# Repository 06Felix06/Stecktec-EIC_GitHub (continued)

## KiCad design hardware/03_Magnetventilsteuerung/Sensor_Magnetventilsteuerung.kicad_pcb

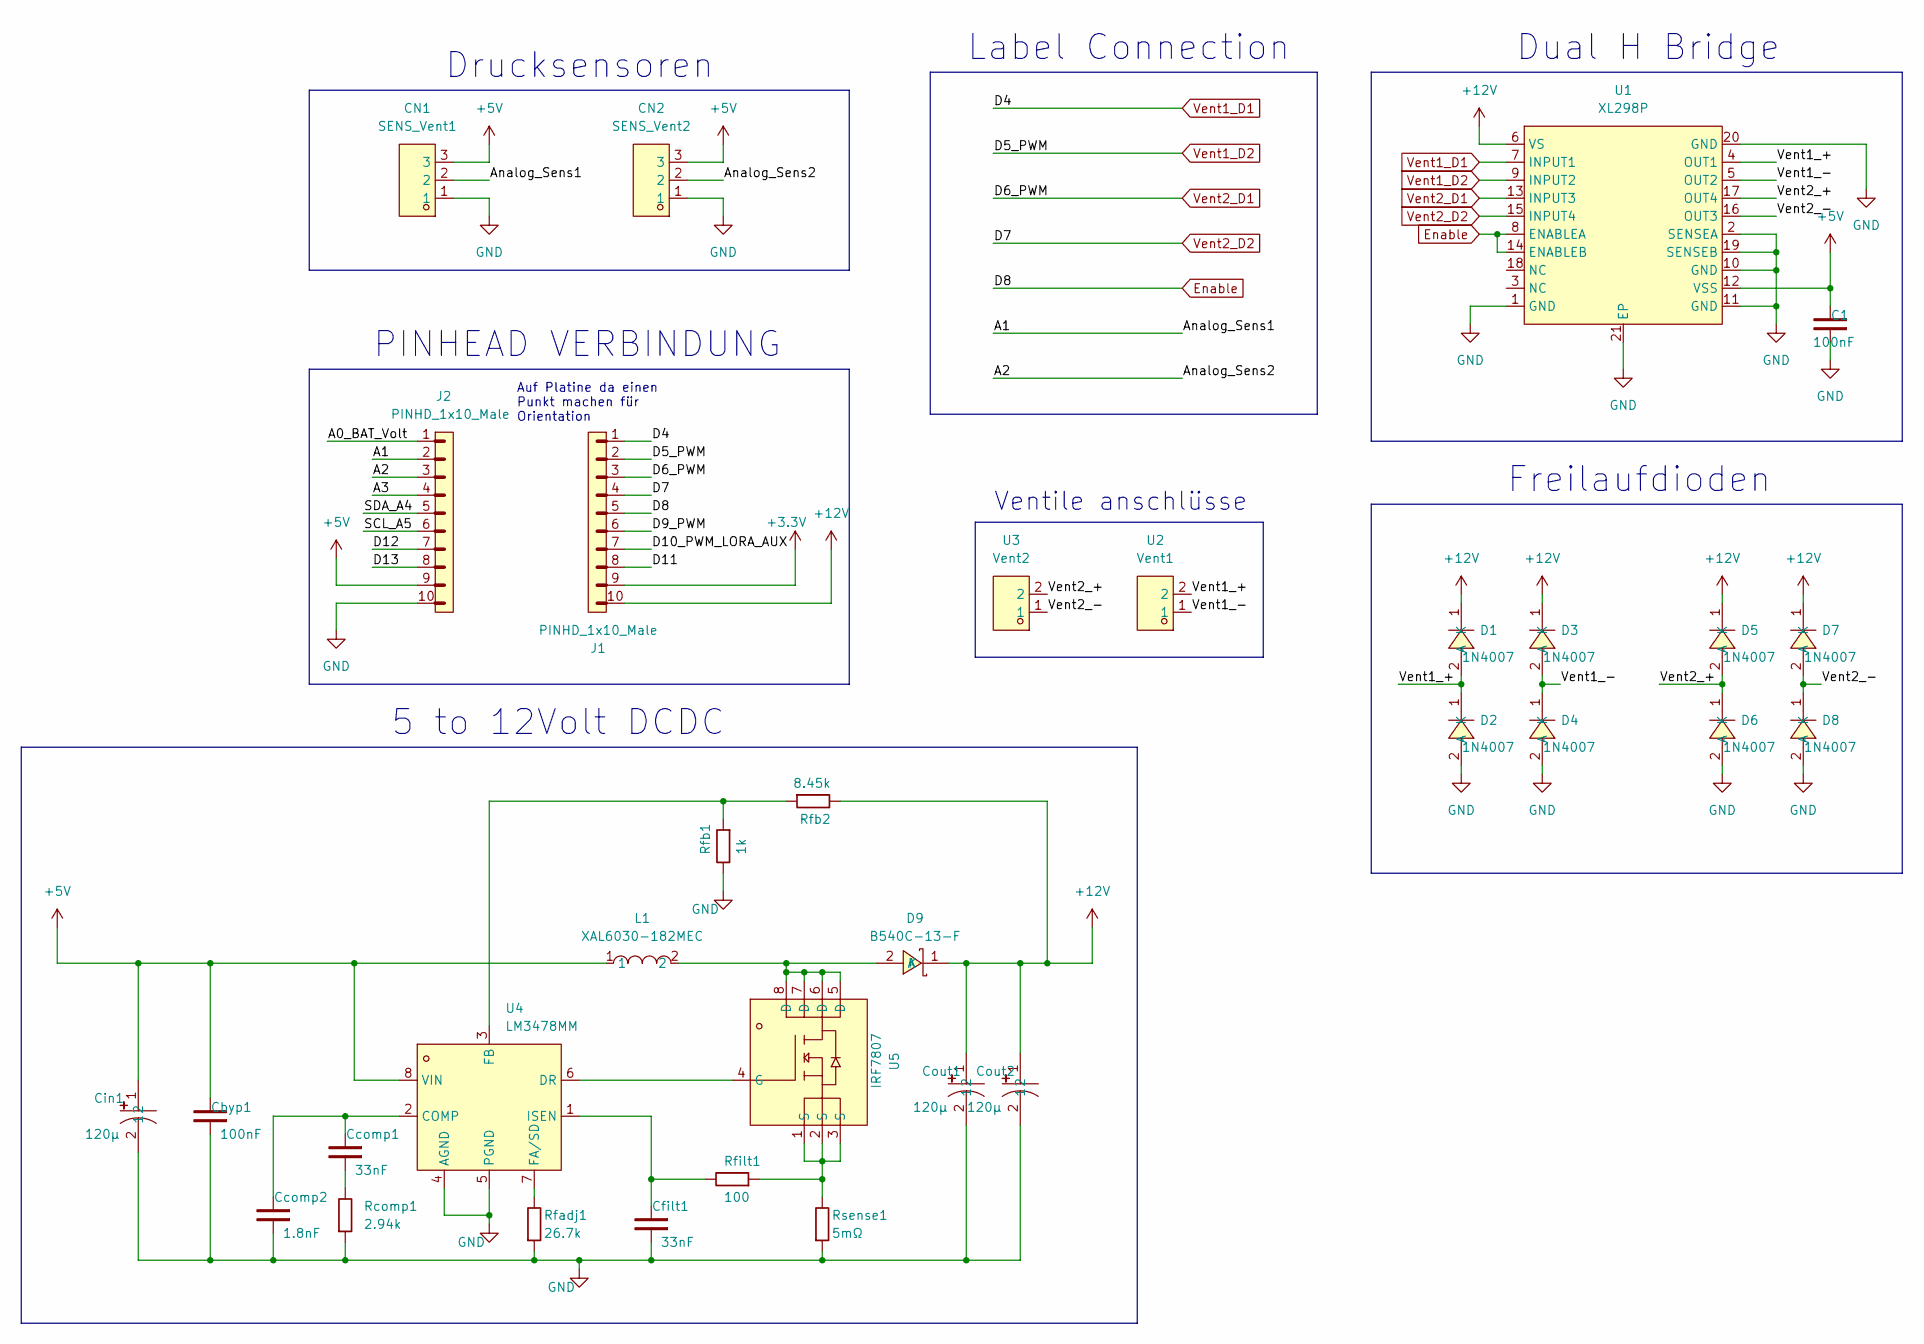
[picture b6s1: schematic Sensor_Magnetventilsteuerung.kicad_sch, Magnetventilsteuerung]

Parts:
C1: 100nF; C_0805_2012Metric
CN1: SENS_Vent1; CONN-TH_B3B-PH-K-S; LCSC Part C131339
CN2: SENS_Vent2; CONN-TH_B3B-PH-K-S; LCSC Part C131339
Cbyp1: 100nF; C_0805_2012Metric
Ccomp1: 33nF; C_0805_2012Metric
Ccomp2: 1.8nF; C_0805_2012Metric
Cfilt1: 33nF; C_0805_2012Metric
Cin1: 120µ; CAP-TH_BD6.3-P2.50-D1.0-FD; LCSC Part C442997
Cout1, Cout2: 120µ; CAP-TH_BD6.3-P2.50-D1.0-FD; LCSC Part C442997
D1, D2, D3, D4, D5, D6, D7, D8: 1N4007; SMA_L4.3-W2.5-LS5.0-RD; LCSC Part C727081
D9: B540C-13-F; SMC_L7.1-W6.2-LS8.1-RD; LCSC Part C72264
J1, J2: PINHD_1x10_Male; PinHeader_1x10_P2.54mm_Vertical
L1: XAL6030-182MEC; IND-SMD_L6.6-W6.4; LCSC Part C19191693
Rcomp1: 2.94k; R_0805_2012Metric
Rfadj1: 26.7k; R_0805_2012Metric
Rfb1: 1k; R_0805_2012Metric
Rfb2: 8.45k; R_0805_2012Metric
Rfilt1: 100; R_0805_2012Metric
Rsense1: 5mΩ; R_0805_2012Metric
U1: XL298P; HSOP-20_L15.9-W11.0-P1.27-LS14.2-BL-EP; LCSC Part C17179540
U2: Vent1; CONN-TH_2P-P5.00_MX127-5.0-02P-GN01-CU-Y-A; LCSC Part C5188440
U3: Vent2; CONN-TH_2P-P5.00_MX127-5.0-02P-GN01-CU-Y-A; LCSC Part C5188440
U4: LM3478MM; VSSOP-8_L3.0-W3.0-P0.65-LS5.0-BL; LCSC Part C9404
U5: IRF7807; SOP-8_L4.9-W3.9-P1.27-LS6.0-BL; LCSC Part C5350865

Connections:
+3.3V: J1.9
+5V: C1.1, CN1.3, CN2.3, Cbyp1.1, Cin1.1, J2.9, L1.1, U1.12 (VSS), U4.8 (VIN)
+12V: Cout1.1, Cout2.1, D1.1 (K), D3.1 (K), D5.1 (K), D7.1 (K), D9.1 (K), J1.10, Rfb2.2, U1.6 (VS)
/A0_BAT_Volt: J2.1
/A1: CN1.2, J2.2
/A2: CN2.2, J2.3
/A3: J2.4
/D9_PWM: J1.6
/D10_PWM_LORA_AUX: J1.7
/D11: J1.8
/D12: J2.7
/D13: J2.8
/SCL_A5: J2.6
/SDA_A4: J2.5
/Vent1_+: D1.2 (A), D2.1 (K), U1.4 (OUT1), U2.2
/Vent1_-: D3.2 (A), D4.1 (K), U1.5 (OUT2), U2.1
/Vent2_+: D5.2 (A), D6.1 (K), U1.17 (OUT4), U3.2
/Vent2_-: D7.2 (A), D8.1 (K), U1.16 (OUT3), U3.1
Enable: J1.5, U1.8 (ENABLEA), U1.14 (ENABLEB)
GND: C1.2, CN1.1, CN2.1, Cbyp1.2, Ccomp2.2, Cfilt1.2, Cin1.2, Cout1.2, Cout2.2, D2.2 (A), D4.2 (A), D6.2 (A), D8.2 (A), J2.10, Rcomp1.1, Rfadj1.1, Rfb1.2, Rsense1.1, U1.1 (GND), U1.2 (SENSEA), U1.10 (GND), U1.11 (GND), U1.19 (SENSEB), U1.20 (GND), U1.21 (EP), U4.4 (AGND), U4.5 (PGND)
unnamed: Ccomp1.2, Rcomp1.2
unnamed: D9.2 (A), L1.2, U5.5 (D), U5.6 (D), U5.7 (D), U5.8 (D)
unnamed: Rfilt1.1, Rsense1.2, U5.1 (S), U5.2 (S), U5.3 (S)
unnamed: Ccomp1.1, Ccomp2.1, U4.2 (COMP)
unnamed: U4.6 (DR), U5.4 (G)
unnamed: Rfadj1.2, U4.7 (FA/SD)
unnamed: Rfb1.1, Rfb2.1, U4.3 (FB)
unnamed: Cfilt1.1, Rfilt1.2, U4.1 (ISEN)
Vent1_D1: J1.1, U1.7 (INPUT1)
Vent1_D2: J1.2, U1.9 (INPUT2)
Vent2_D1: J1.3, U1.13 (INPUT3)
Vent2_D2: J1.4, U1.15 (INPUT4)

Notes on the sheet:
5 to 12Volt DCDC
Auf Platine da einen Punkt machen für Orientation
Drucksensoren
Ventile anschlüsse
Label Connection
Freilaufdioden
PINHEAD VERBINDUNG
Dual H Bridge

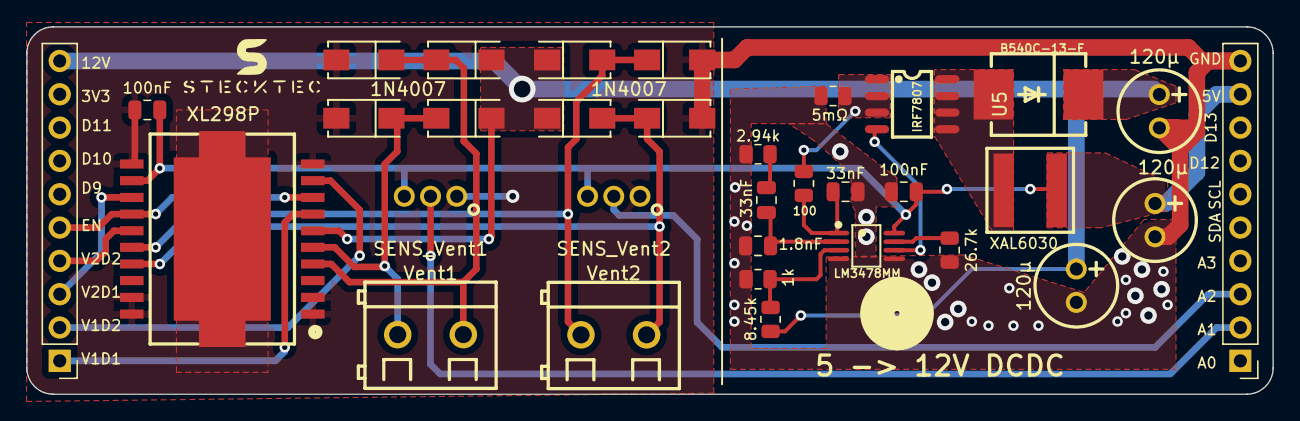
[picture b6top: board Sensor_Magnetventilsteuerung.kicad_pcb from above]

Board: 2 copper layers, 95.0 x 28.0 mm, 33 parts (0 on the bottom side), 22 nets.

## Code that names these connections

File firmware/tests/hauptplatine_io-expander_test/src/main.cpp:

#include <Arduino.h>
#include <Adafruit_MCP23X17.h>

// MCP23017 Pins (GPA0-GPA7, GPB0-GPB7)
#define VENT1_D2 0 // Valve 1 Direction 2
#define VENT1_D1 1 // Valve 1 Direction 1
#define VENT2_D2 2 // Valve 2 Direction 2
#define VENT2_D1 3 // Valve 2 Direction 1
#define VENT3_D2 4 // Valve 3 Direction 2
#define VENT3_D1 5 // Valve 3 Direction 1
#define VENT4_D2 6 // Valve 4 Direction 2
#define VENT4_D1 7 // Valve 4 Direction 1

// Arduino Pins
#define ENABLE_PIN 3 // Shared enable pin (D3)

// Direction control variables (set these externally)
bool Vent1_State = true; // Example: false = "-+", true = "+-"
bool Vent2_State = false;
bool Vent3_State = true;
bool Vent4_State = false;

Adafruit_MCP23X17 mcp;

void setup()
{
    Serial.begin(9600);

    // Initialize MCP23017 at address 0x27
    if (!mcp.begin_I2C(0x27))
    {
        Serial.println("MCP23017 not found!");
        while (1)
            ;
    }

    // Configure all Valve control pins as OUTPUT
    mcp.pinMode(VENT1_D1, OUTPUT);
    mcp.pinMode(VENT1_D2, OUTPUT);
    mcp.pinMode(VENT2_D1, OUTPUT);
    mcp.pinMode(VENT2_D2, OUTPUT);
    mcp.pinMode(VENT3_D1, OUTPUT);
    mcp.pinMode(VENT3_D2, OUTPUT);
    mcp.pinMode(VENT4_D1, OUTPUT);
    mcp.pinMode(VENT4_D2, OUTPUT);

    // Configure enable pin (HIGH = Valves enabled)
    pinMode(ENABLE_PIN, OUTPUT);
    digitalWrite(ENABLE_PIN, LOW);

    Serial.println("System Ready");
}

void updateVent(uint8_t D1_pin, uint8_t D2_pin, bool state)
{
    if (state == true)
    {
        digitalWrite(ENABLE_PIN, LOW);
        mcp.digitalWrite(D1_pin, LOW);
        Serial.print("D1_pin true LOW: ");
        Serial.println(D1_pin);
        delay(10);
        mcp.digitalWrite(D2_pin, HIGH);
        Serial.print("D2_pin true HIGH: ");
        Serial.println(D2_pin);
        digitalWrite(ENABLE_PIN, HIGH);
    }
    else if (state == false)
    {
        digitalWrite(ENABLE_PIN, LOW);
        mcp.digitalWrite(D2_pin, LOW);
        Serial.print("D2_pin false LOW: ");
        Serial.println(D2_pin);
        delay(10);
        mcp.digitalWrite(D1_pin, HIGH);
        Serial.print("D1_pin false HIGH: ");
        Serial.println(D1_pin);
        digitalWrite(ENABLE_PIN, HIGH);
    }
}

void loop()
{
    // Update Valve directions based on boolean states
    // updateVent(VENT1_D1, VENT1_D2, Vent1_State); // Valve 1 //Hardware wahrschienlich defekt
    updateVent(VENT2_D1, VENT2_D2, Vent2_State); // Valve 2
    updateVent(VENT3_D1, VENT3_D2, Vent3_State); // Valve 3
    // updateVent(VENT4_D1, VENT4_D2, Vent4_State); // Valve 4 //Hardware wahrschienlich defekt
    Vent2_State = !Vent2_State; // Toggle state for testing
    Vent3_State = !Vent3_State; // Toggle state for testing
    delay(2000);
}
